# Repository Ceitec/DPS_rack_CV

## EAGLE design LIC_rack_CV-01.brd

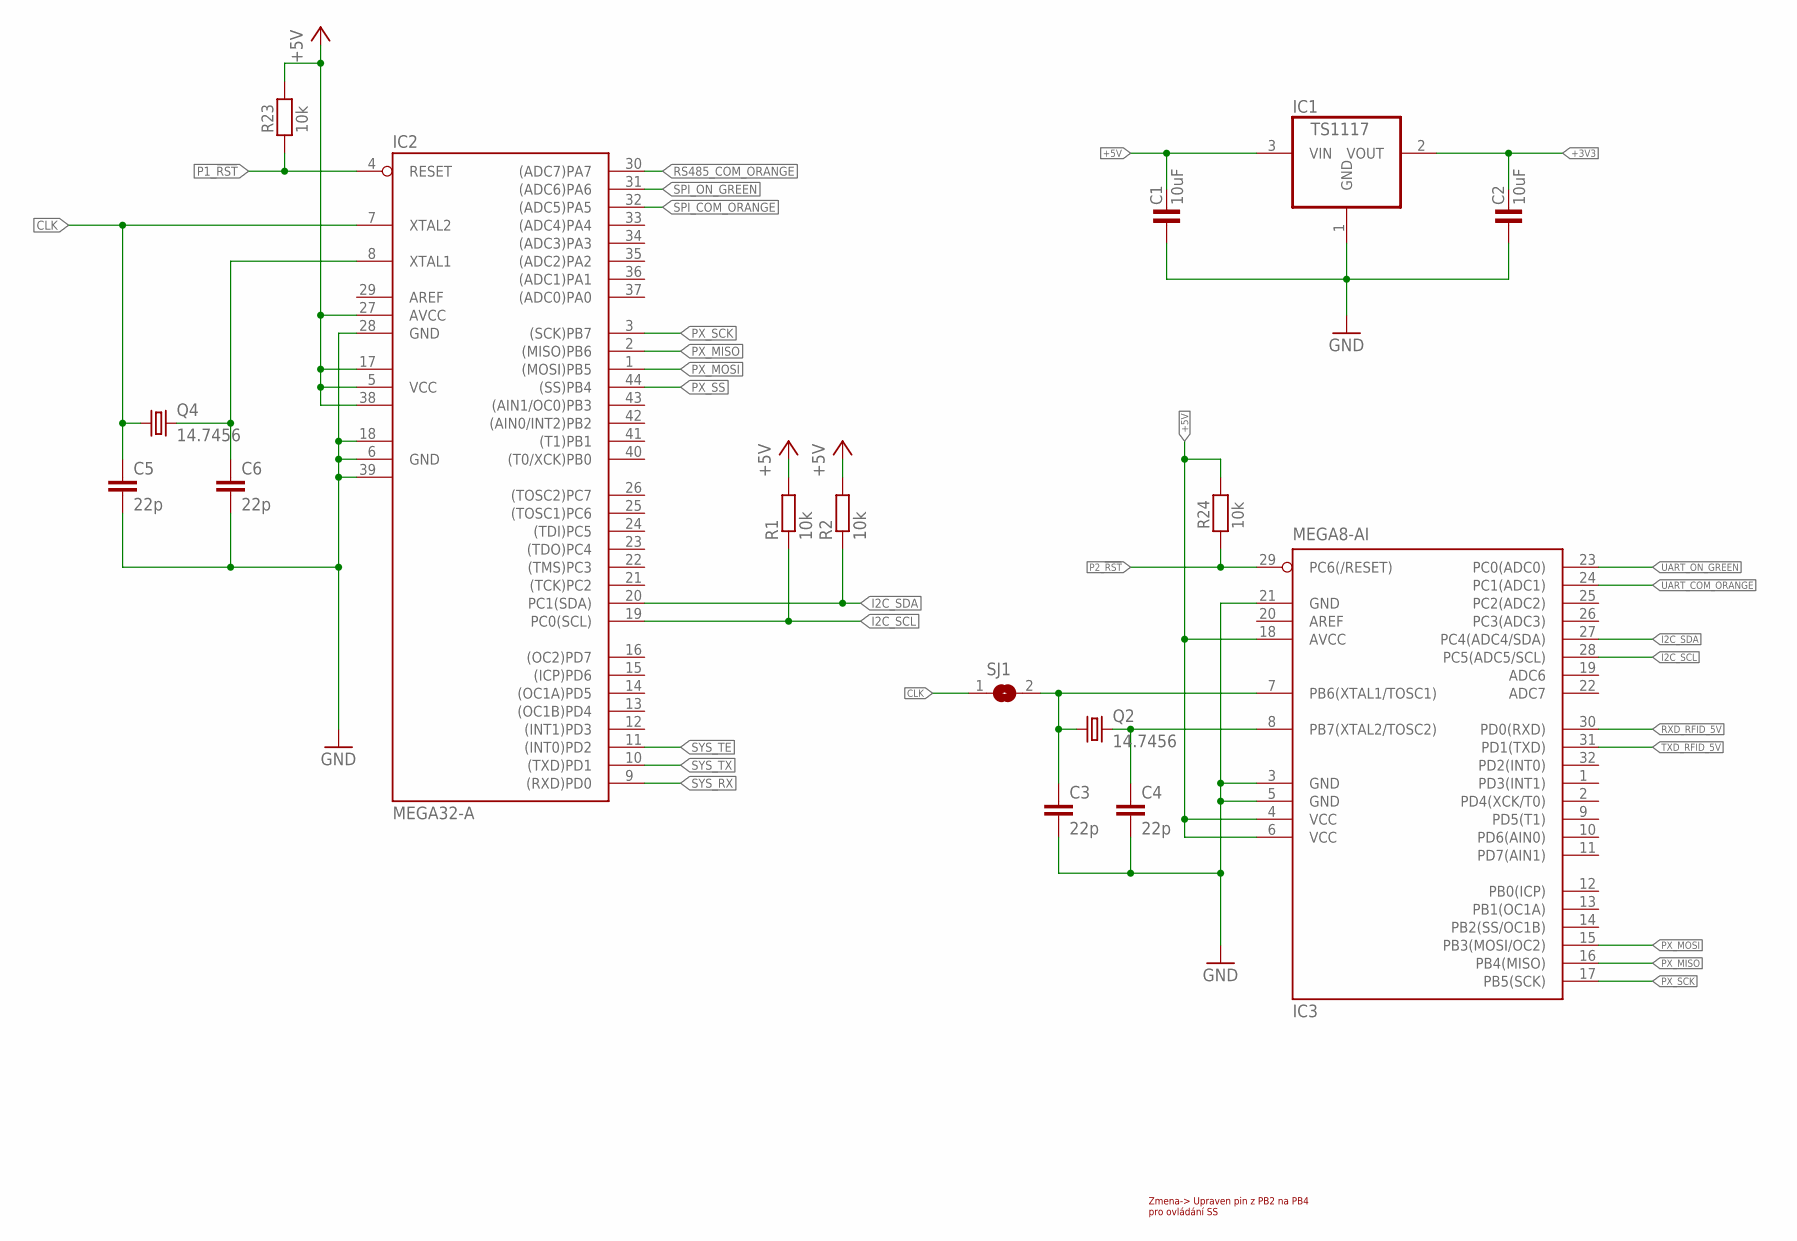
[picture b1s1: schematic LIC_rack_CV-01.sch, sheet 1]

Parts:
C1, C2: 10uF; 1206
C3, C4, C5, C6: 22p; C0805
IC1: TS1117; SOT223
IC2: MEGA32-A; TQFP44
IC3: MEGA8-AI; TQFP32-08
Q2, Q4: 14.7456; HC49U70
R1, R2: 10k; R1206
R23, R24: 10k; 1206
SJ1: SJ

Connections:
+3V3: C2.2, IC1.2 (VOUT); also elsewhere on the board
+5V: C1.2, IC1.3 (VIN), IC2.5 (VCC), IC2.17 (VCC1), IC2.27 (AVCC), IC2.38 (VCC2), IC3.4 (VCC), IC3.6 (VCC), IC3.18 (AVCC), R1.2, R2.2, R23.2, R24.2; also elsewhere on the board
CLK: C5.1, IC2.7 (XTAL2), Q4.1, SJ1.1
CLK1: C3.1, IC3.7 (PB6(XTAL1/TOSC1)), Q2.1, SJ1.2
GND: C1.1, C2.1, C3.2, C4.2, C5.2, C6.2, IC1.1 (GND), IC2.6 (GND), IC2.18 (GND1), IC2.28 (GND), IC2.39 (GND2), IC3.3 (GND), IC3.5 (GND), IC3.21 (GND); also elsewhere on the board
I2C_SCL: IC2.19 (PC0(SCL)), IC3.28 (PC5(ADC5/SCL)), R1.1
I2C_SDA: IC2.20 (PC1(SDA)), IC3.27 (PC4(ADC4/SDA)), R2.1
unnamed: C4.1, IC3.8 (PB7(XTAL2/TOSC2)), Q2.2
unnamed: C6.1, IC2.8 (XTAL1), Q4.2
P1_!RST: IC2.4 (RESET), R23.1; also elsewhere on the board
P2_!RST: IC3.29 (PC6(/RESET)), R24.1; also elsewhere on the board
PX_MISO: IC2.2 ((MISO)PB6), IC3.16 (PB4(MISO)); also elsewhere on the board
PX_MOSI: IC2.1 ((MOSI)PB5), IC3.15 (PB3(MOSI/OC2)); also elsewhere on the board
PX_SCK: IC2.3 ((SCK)PB7), IC3.17 (PB5(SCK)); also elsewhere on the board
PX_SS: IC2.44 ((SS)PB4); also elsewhere on the board
RS485_COM_ORANGE: IC2.30 ((ADC7)PA7); also elsewhere on the board
RXD_RFID_5V: IC3.30 (PD0(RXD)); also elsewhere on the board
SPI_COM_ORANGE: IC2.32 ((ADC5)PA5); also elsewhere on the board
SPI_ON_GREEN: IC2.31 ((ADC6)PA6); also elsewhere on the board
SYS_RX: IC2.9 ((RXD)PD0); also elsewhere on the board
SYS_TE: IC2.11 ((INT0)PD2); also elsewhere on the board
SYS_TX: IC2.10 ((TXD)PD1); also elsewhere on the board
TXD_RFID_5V: IC3.31 (PD1(TXD)); also elsewhere on the board
UART_COM_ORANGE: IC3.24 (PC1(ADC1)); also elsewhere on the board
UART_ON_GREEN: IC3.23 (PC0(ADC0)); also elsewhere on the board

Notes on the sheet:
Zmena-> Upraven pin z PB2 na PB4 pro ovládání SS

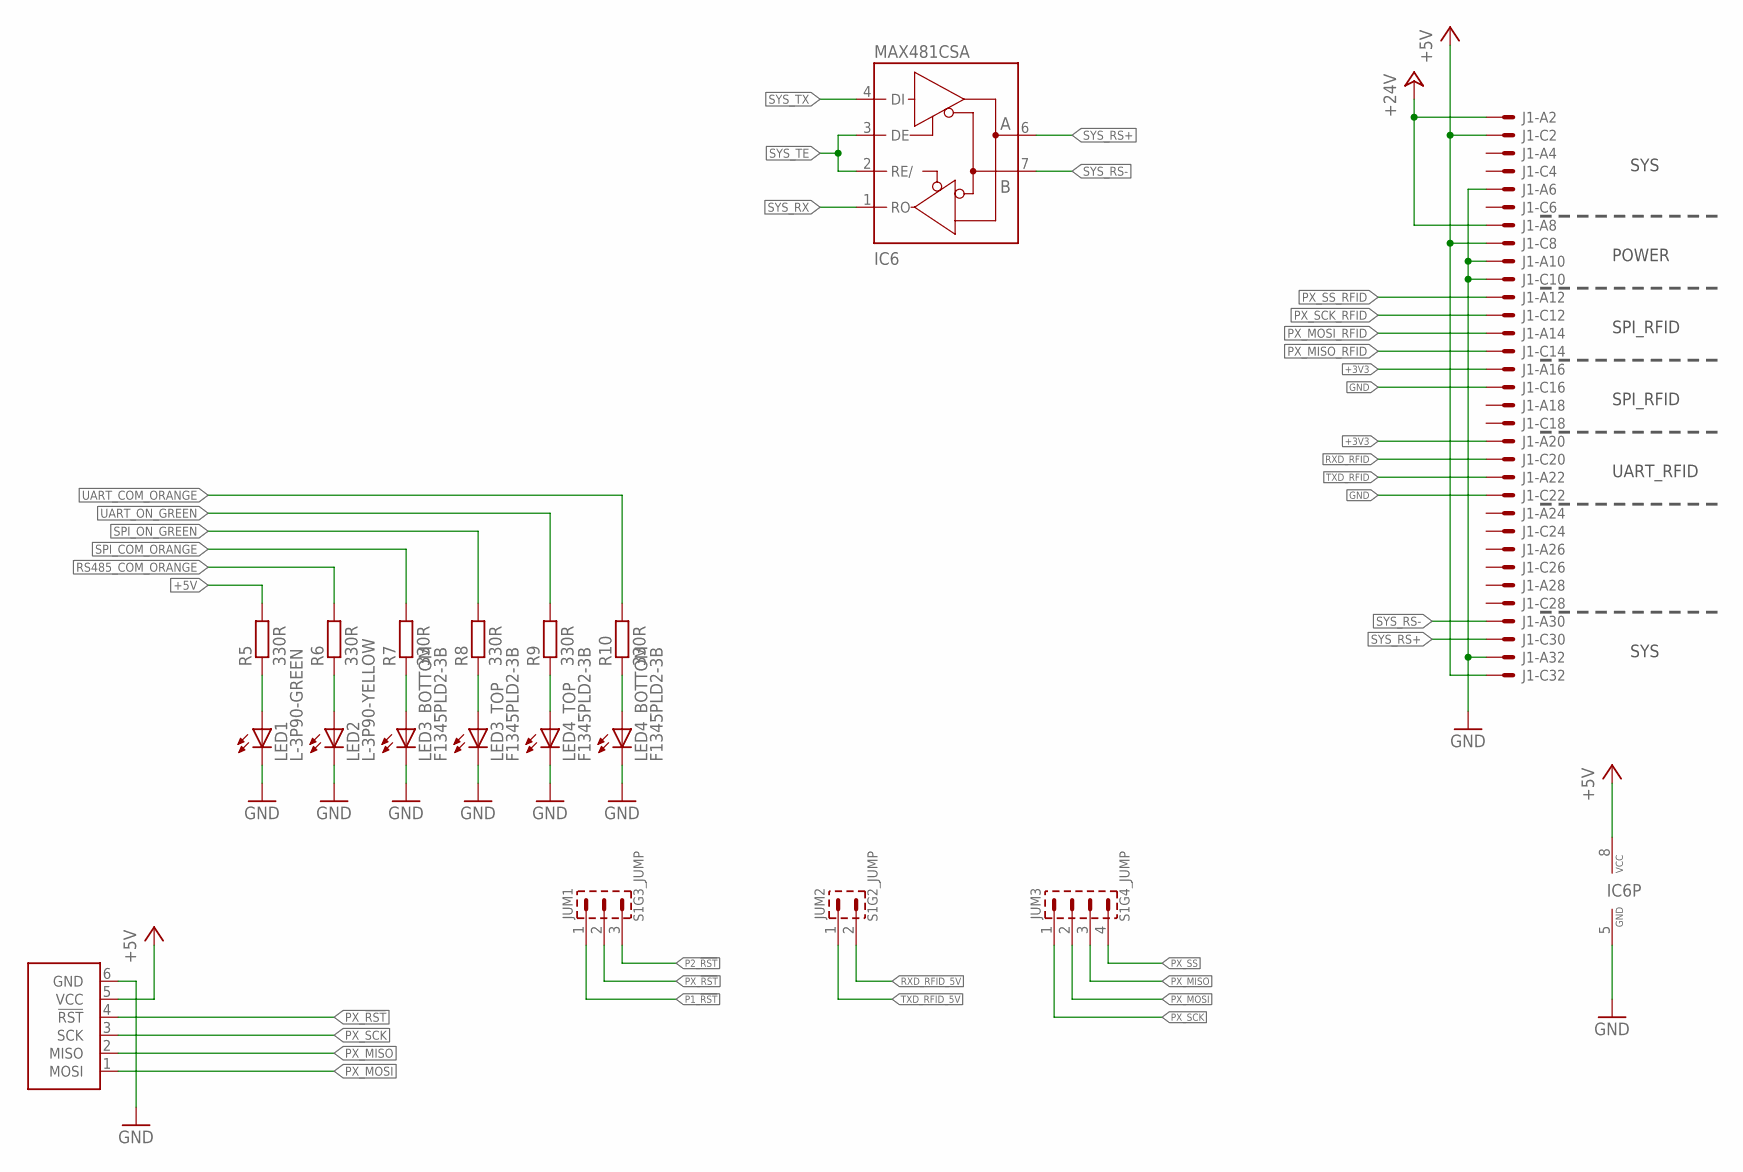
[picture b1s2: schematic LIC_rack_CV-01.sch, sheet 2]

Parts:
IC6: MAX481CSA; SO08
J1: VG32SP; VG32P
JUM1: S1G3_JUMP; S1G3_JUM
JUM2: S1G2_JUMP; S1G2_JUM
JUM3: S1G4_JUMP; S1G4_JUM
LED1: L-3P90-GREEN; L-3P90
LED2: L-3P90-YELLOW; L-3P90
LED3, LED4: F1345PLD2-3B
R5, R6, R7, R8, R9, R10: 330R; R1206
U1: ATPROG-V; 6410-06

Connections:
+3V3: J1.A16 (MS), J1.A20 (MS); also elsewhere on the board
+5V: IC6.8 (VCC), J1.C2 (MS), J1.C8 (MS), J1.C32 (MSV), R5.2, U1.5 (VCC); also elsewhere on the board
+24V: J1.A2 (MS), J1.A8 (MS)
GND: IC6.5 (GND), J1.A6 (MS), J1.A10 (MS), J1.A32 (MS), J1.C10 (MS), J1.C16 (MS), J1.C22 (MS), LED1.K (C), LED2.K (C), LED3.1K (C), LED3.2K (C), LED4.1K (C), LED4.2K (C), U1.6 (GND); also elsewhere on the board
unnamed: LED2.A, R6.1
unnamed: LED1.A, R5.1
unnamed: LED4.1A (A), R10.1
unnamed: LED4.2A (A), R9.1
unnamed: LED3.2A (A), R8.1
unnamed: LED3.1A (A), R7.1
P1_!RST: JUM1.1; also elsewhere on the board
P2_!RST: JUM1.3; also elsewhere on the board
PX_!RST: JUM1.2, U1.4 (!RST)
PX_MISO: JUM3.3, U1.2 (MISO); also elsewhere on the board
PX_MISO_RFID: J1.C14 (MS); also elsewhere on the board
PX_MOSI: JUM3.2, U1.1 (MOSI); also elsewhere on the board
PX_MOSI_RFID: J1.A14 (MS); also elsewhere on the board
PX_SCK: JUM3.1, U1.3 (SCK); also elsewhere on the board
PX_SCK_RFID: J1.C12 (MS); also elsewhere on the board
PX_SS: JUM3.4; also elsewhere on the board
PX_SS_RFID: J1.A12 (MS); also elsewhere on the board
RS485_COM_ORANGE: R6.2; also elsewhere on the board
RXD_RFID: J1.C20 (MS); also elsewhere on the board
RXD_RFID_5V: JUM2.2; also elsewhere on the board
SPI_COM_ORANGE: R7.2; also elsewhere on the board
SPI_ON_GREEN: R8.2; also elsewhere on the board
SYS_RS+: IC6.6 (A), J1.C30 (MS)
SYS_RS-: IC6.7 (B), J1.A30 (MS)
SYS_RX: IC6.1 (RO); also elsewhere on the board
SYS_TE: IC6.2 (RE/), IC6.3 (DE); also elsewhere on the board
SYS_TX: IC6.4 (DI); also elsewhere on the board
TXD_RFID: J1.A22 (MS); also elsewhere on the board
TXD_RFID_5V: JUM2.1; also elsewhere on the board
UART_COM_ORANGE: R10.2; also elsewhere on the board
UART_ON_GREEN: R9.2; also elsewhere on the board

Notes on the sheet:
SYS
POWER
SPI_RFID
UART_RFID

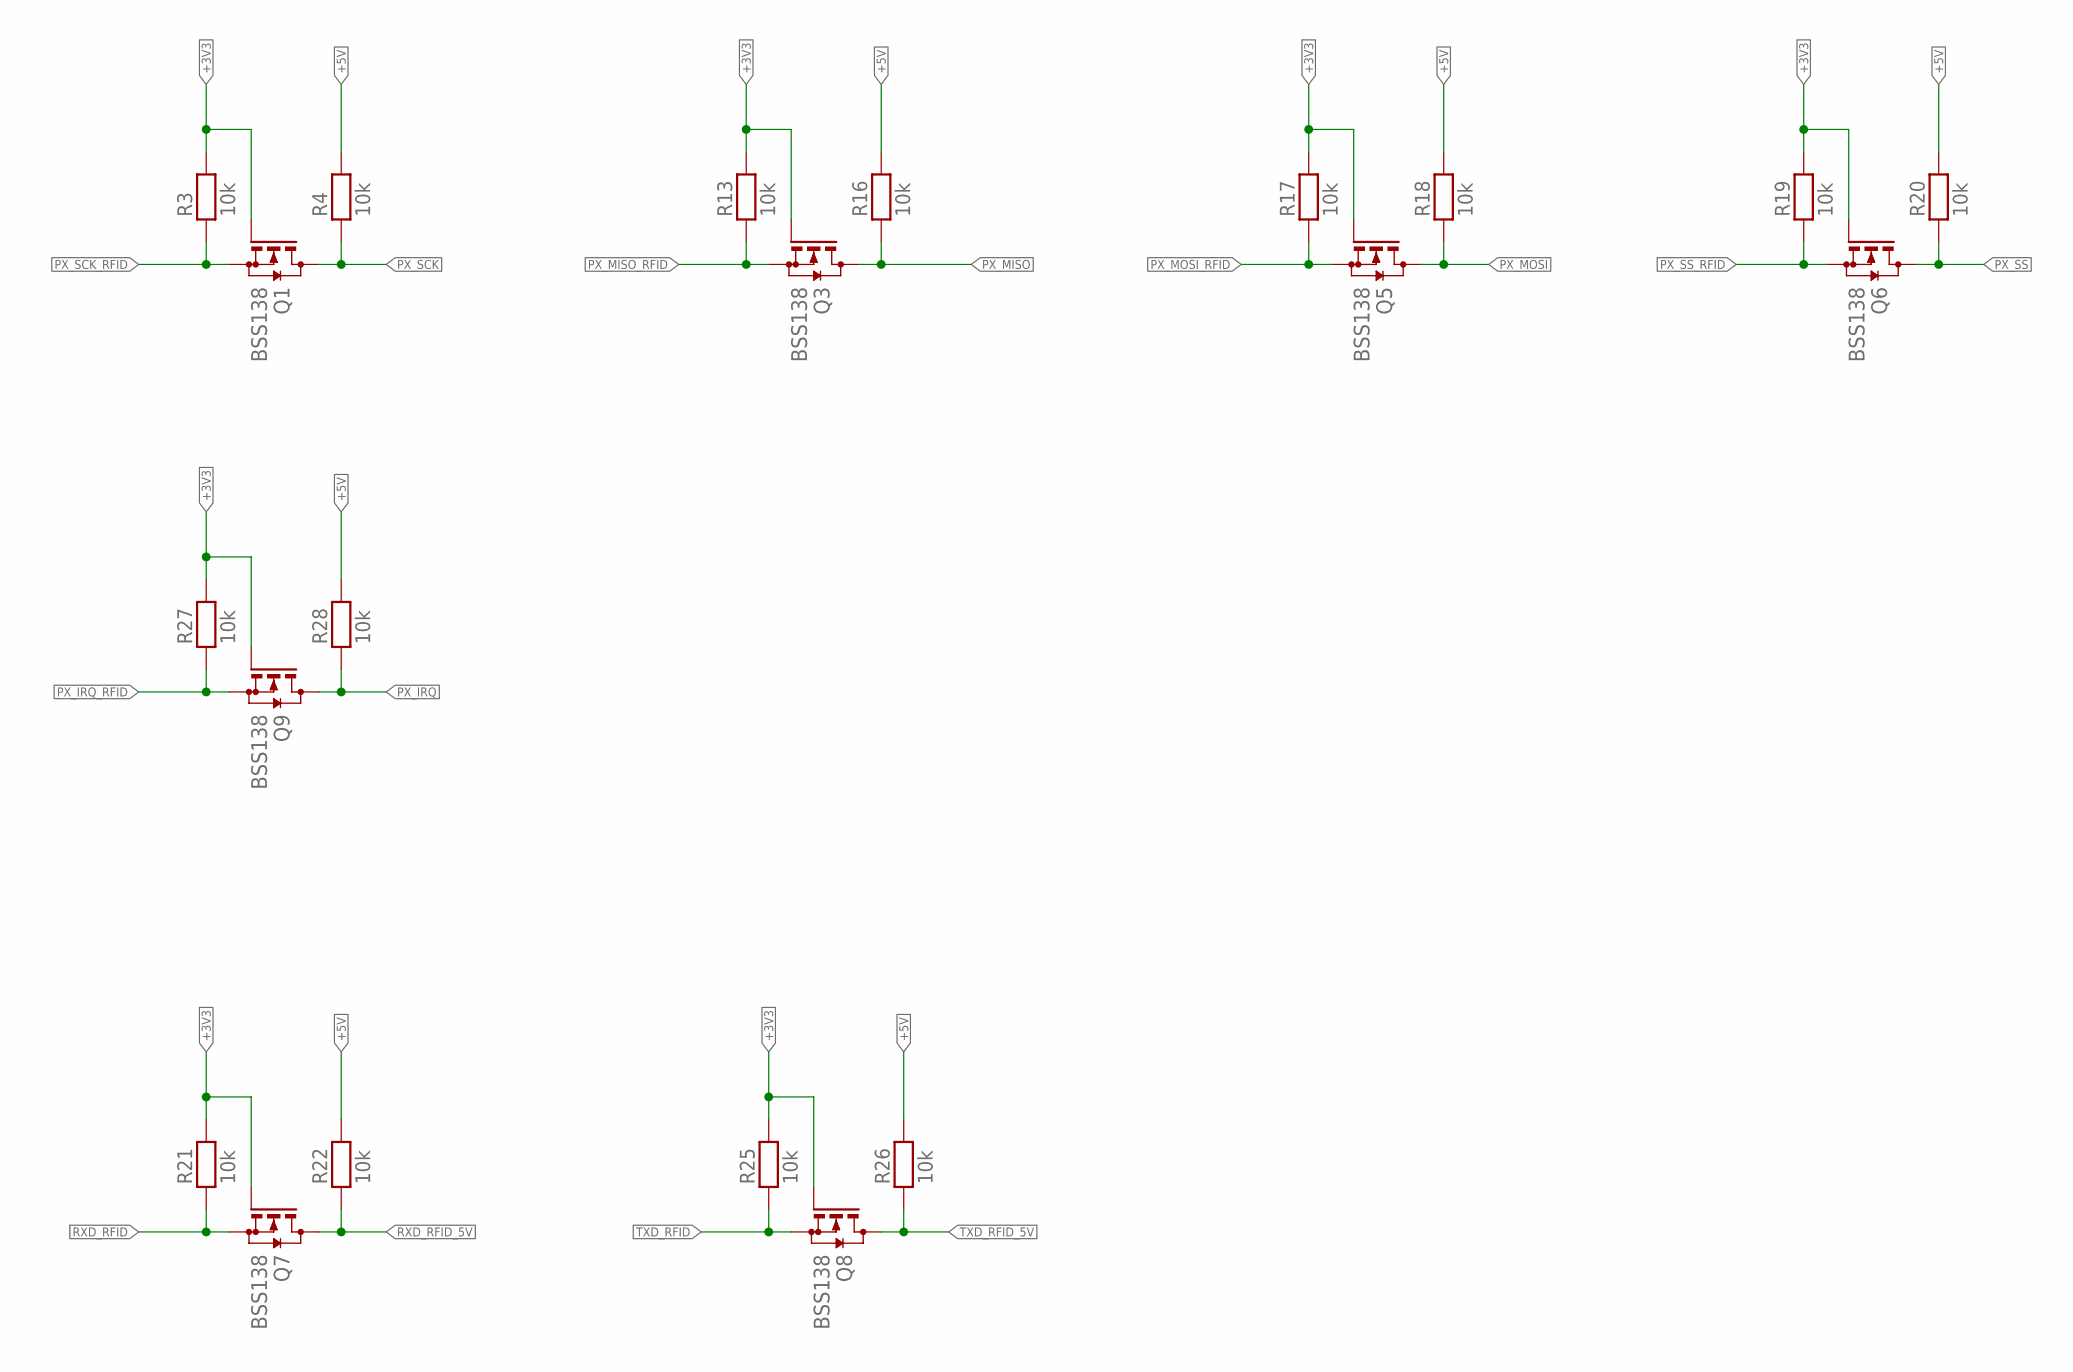
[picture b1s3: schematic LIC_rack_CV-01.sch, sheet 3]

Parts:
Q1, Q3, Q5, Q6, Q7, Q8, Q9: BSS138; SOT23
R3, R4, R13, R16, R17, R18, R19, R20, R21, R22, R25, R26, R27, R28: 10k; 1206

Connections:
+3V3: Q1.1 (G), Q3.1 (G), Q5.1 (G), Q6.1 (G), Q7.1 (G), Q8.1 (G), Q9.1 (G), R3.2, R13.2, R17.2, R19.2, R21.2, R25.2, R27.2; also elsewhere on the board
+5V: R4.2, R16.2, R18.2, R20.2, R22.2, R26.2, R28.2; also elsewhere on the board
PX_IRQ: Q9.3 (D), R28.1
PX_IRQ_RFID: Q9.2 (S), R27.1
PX_MISO: Q3.3 (D), R16.1; also elsewhere on the board
PX_MISO_RFID: Q3.2 (S), R13.1; also elsewhere on the board
PX_MOSI: Q5.3 (D), R18.1; also elsewhere on the board
PX_MOSI_RFID: Q5.2 (S), R17.1; also elsewhere on the board
PX_SCK: Q1.3 (D), R4.1; also elsewhere on the board
PX_SCK_RFID: Q1.2 (S), R3.1; also elsewhere on the board
PX_SS: Q6.3 (D), R20.1; also elsewhere on the board
PX_SS_RFID: Q6.2 (S), R19.1; also elsewhere on the board
RXD_RFID: Q7.2 (S), R21.1; also elsewhere on the board
RXD_RFID_5V: Q7.3 (D), R22.1; also elsewhere on the board
TXD_RFID: Q8.2 (S), R25.1; also elsewhere on the board
TXD_RFID_5V: Q8.3 (D), R26.1; also elsewhere on the board

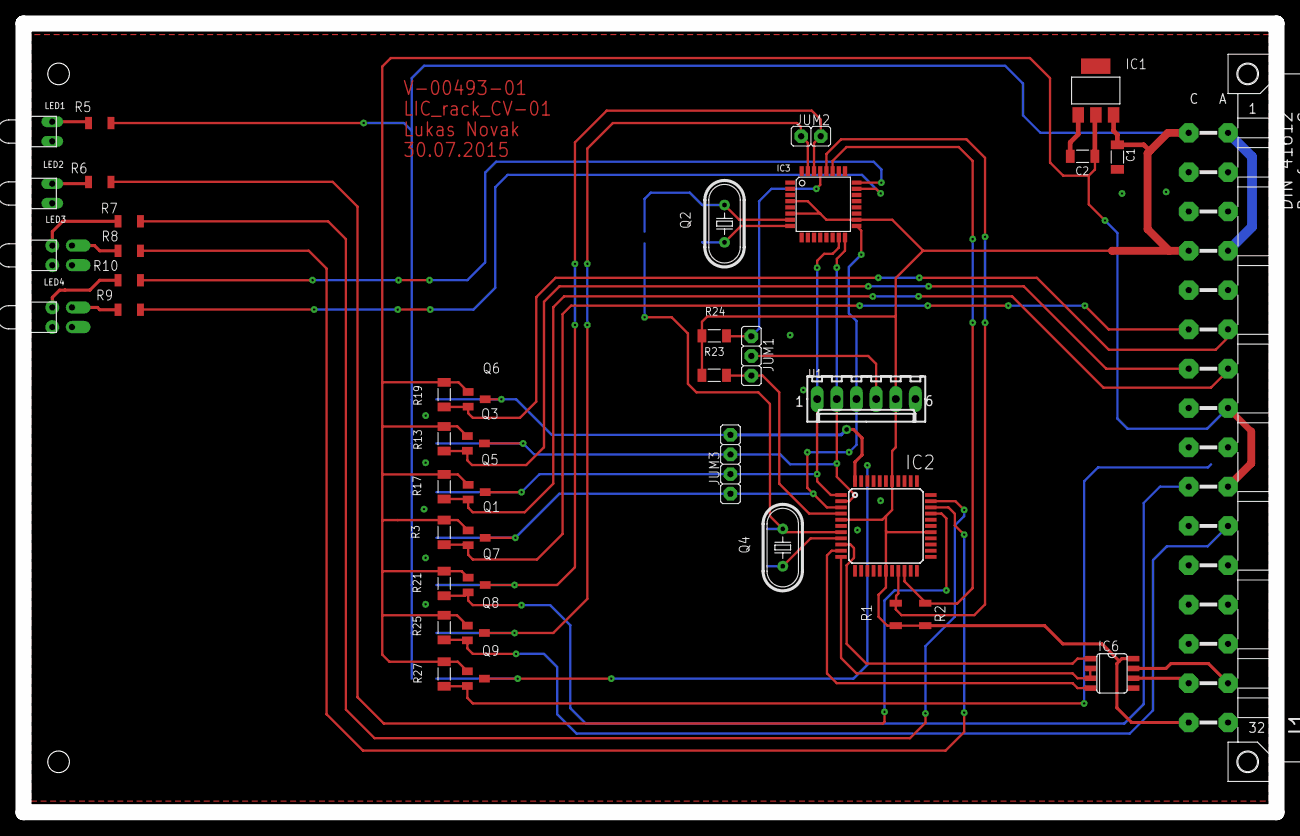
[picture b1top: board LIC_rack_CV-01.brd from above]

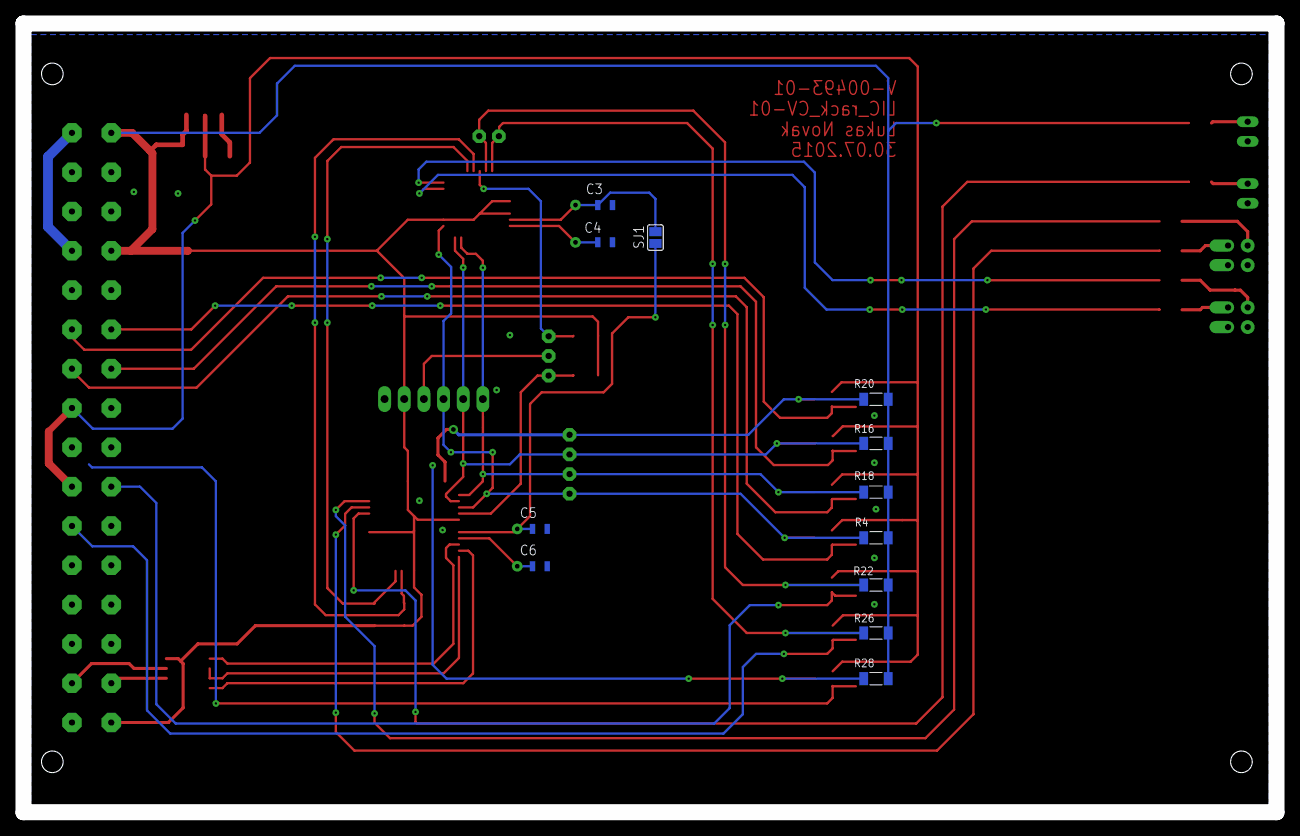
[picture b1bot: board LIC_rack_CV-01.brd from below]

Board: 2 copper layers, 162.0 x 102.0 mm, 53 parts (12 on the bottom side), 43 nets.

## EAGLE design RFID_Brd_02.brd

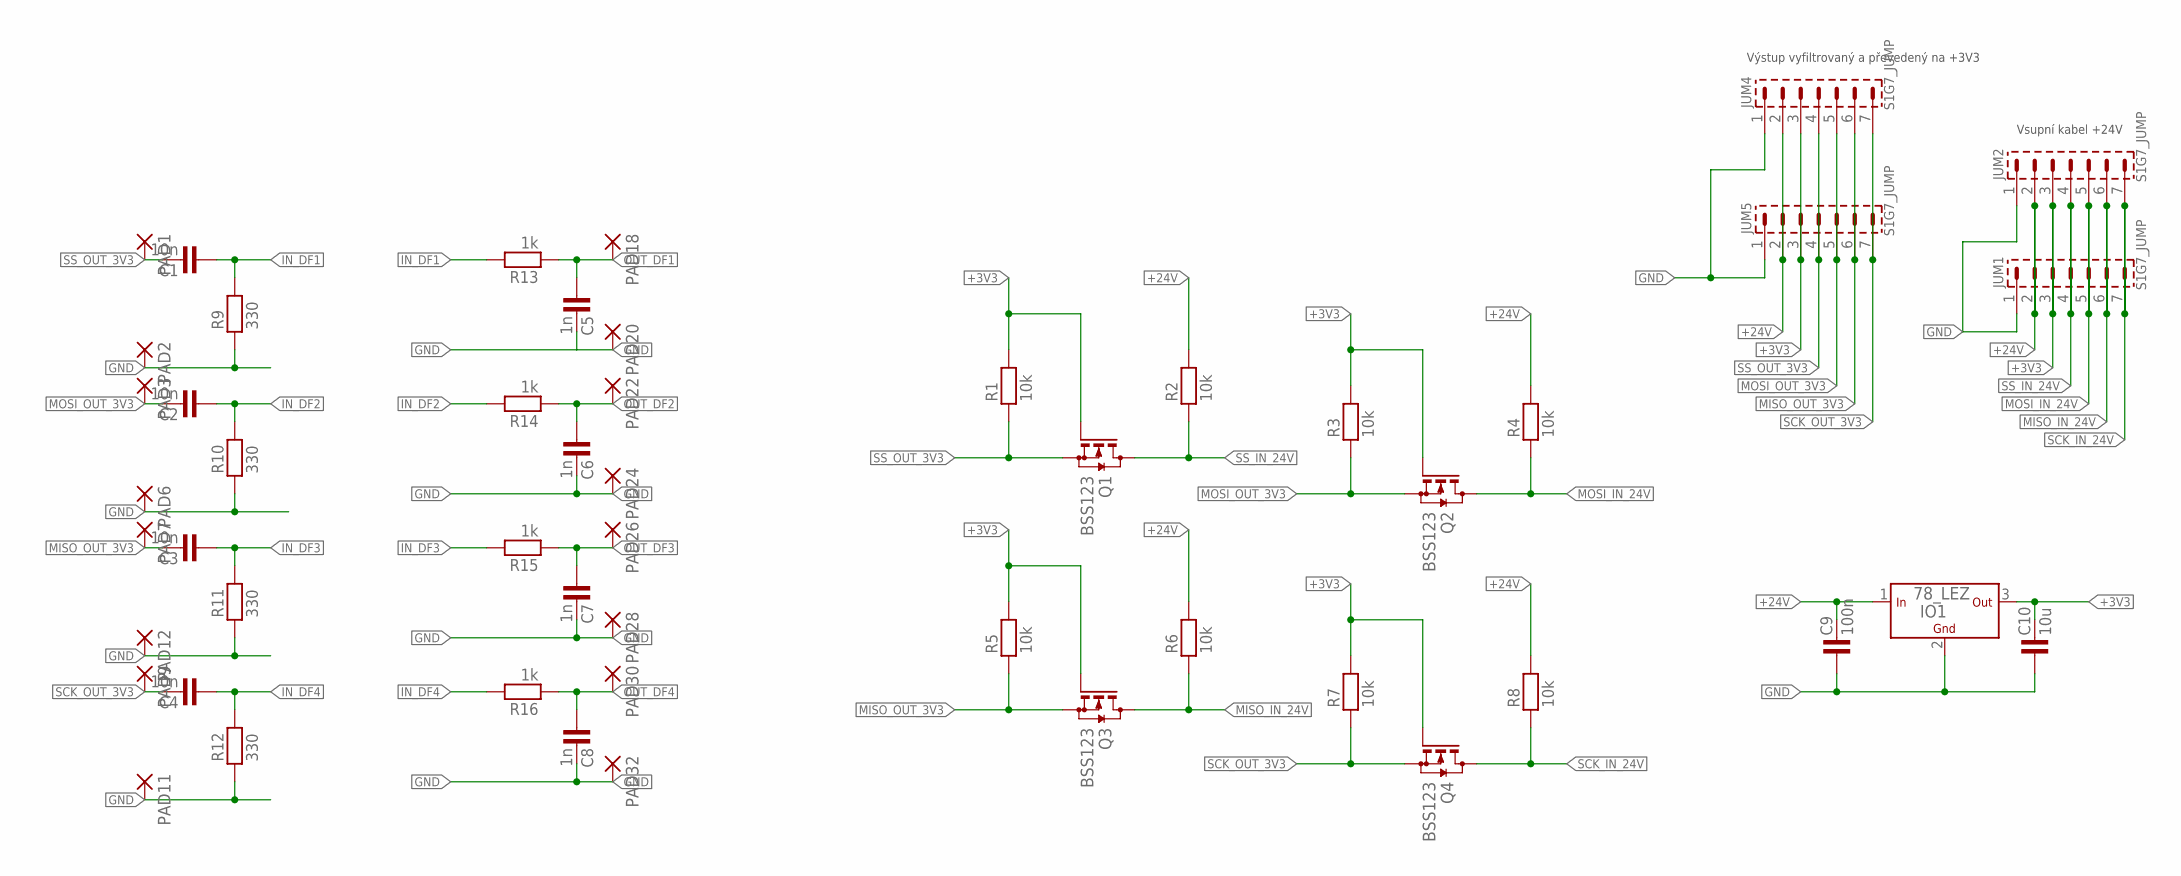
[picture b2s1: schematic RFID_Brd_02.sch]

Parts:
C1, C2, C3, C4: 10n; 1206
C5, C6, C7, C8: 1n; 1206
C9: 100n; 1206
C10: 10u; 1206
IO1: 78_LEZ; TO-220
JUM1, JUM2, JUM4, JUM5: S1G7_JUMP; S1G7_JUM
PAD1, PAD2, PAD3, PAD6, PAD7, PAD9, PAD11, PAD12, PAD18, PAD20, PAD22, PAD24, PAD26, PAD28, PAD30, PAD32: SMD2; SMD1,27-2,54
Q1, Q2, Q3, Q4: BSS123; SOT23
R1, R2, R3, R4, R5, R6, R7, R8: 10k; 1206
R9, R10, R11, R12: 330; 1206
R13, R14, R15, R16: 1k; 1206

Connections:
+3V3: C10.2, IO1.3 (OUT), JUM1.3, JUM2.3, JUM4.3, JUM5.3, Q1.1 (G), Q2.1 (G), Q3.1 (G), Q4.1 (G), R1.2, R3.2, R5.2, R7.2
+24V: C9.2, IO1.1 (IN), JUM1.2, JUM2.2, JUM4.2, JUM5.2, R2.2, R4.2, R6.2, R8.2
GND: C5.2, C6.2, C7.2, C8.2, C9.1, C10.1, IO1.2 (GND), JUM1.1, JUM2.1, JUM4.1, JUM5.1, PAD2.1, PAD6.1, PAD11.1, PAD12.1, PAD20.1, PAD24.1, PAD28.1, PAD32.1, R9.1, R10.1, R11.1, R12.1
IN_DF1: C1.1, R9.2, R13.2
IN_DF2: C2.1, R10.2, R14.2
IN_DF3: C3.1, R11.2, R15.2
IN_DF4: C4.1, R12.2, R16.2
MISO_IN_24V: JUM1.6, JUM2.6, Q3.3 (D), R6.1
MISO_OUT_3V3: C3.2, JUM4.6, JUM5.6, PAD7.1, Q3.2 (S), R5.1
MOSI_IN_24V: JUM1.5, JUM2.5, Q2.3 (D), R4.1
MOSI_OUT_3V3: C2.2, JUM4.5, JUM5.5, PAD3.1, Q2.2 (S), R3.1
OUT_DF1: C5.1, PAD18.1, R13.1
OUT_DF2: C6.1, PAD22.1, R14.1
OUT_DF3: C7.1, PAD26.1, R15.1
OUT_DF4: C8.1, PAD30.1, R16.1
SCK_IN_24V: JUM1.7, JUM2.7, Q4.3 (D), R8.1
SCK_OUT_3V3: C4.2, JUM4.7, JUM5.7, PAD9.1, Q4.2 (S), R7.1
SS_IN_24V: JUM1.4, JUM2.4, Q1.3 (D), R2.1
SS_OUT_3V3: C1.2, JUM4.4, JUM5.4, PAD1.1, Q1.2 (S), R1.1

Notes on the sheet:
Vsupní kabel +24V
Výstup vyfiltrovaný a převedený na +3V3

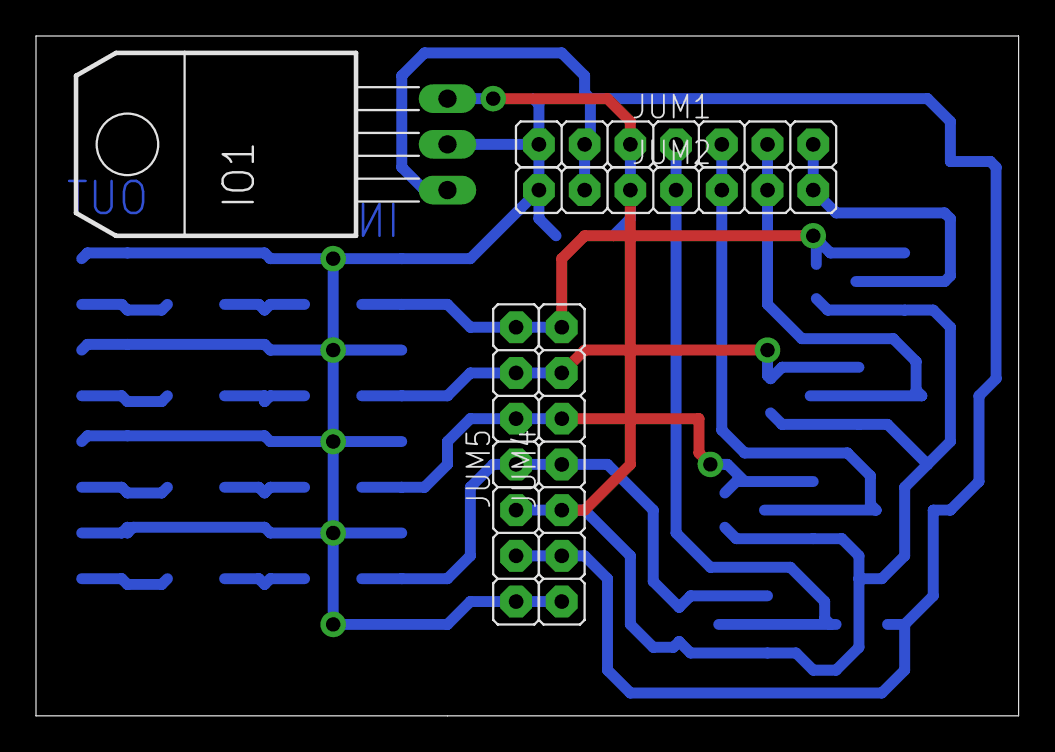
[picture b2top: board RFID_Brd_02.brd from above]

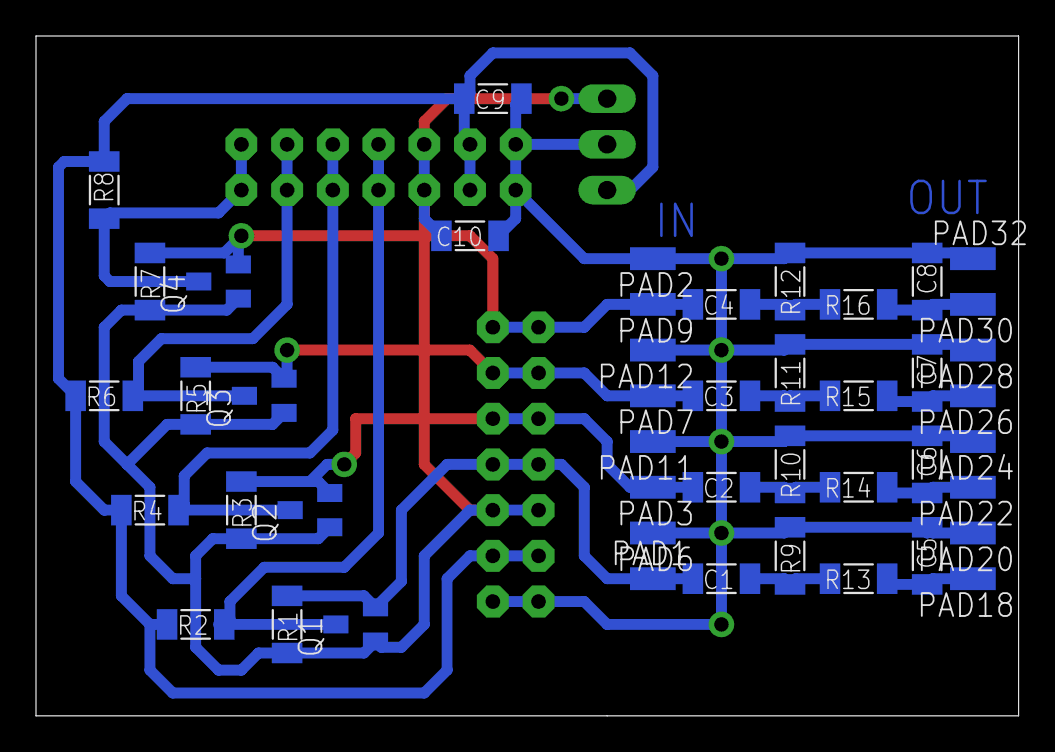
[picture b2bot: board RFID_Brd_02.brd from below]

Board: 2 copper layers, 54.6 x 37.8 mm, 51 parts (46 on the bottom side), 19 nets.

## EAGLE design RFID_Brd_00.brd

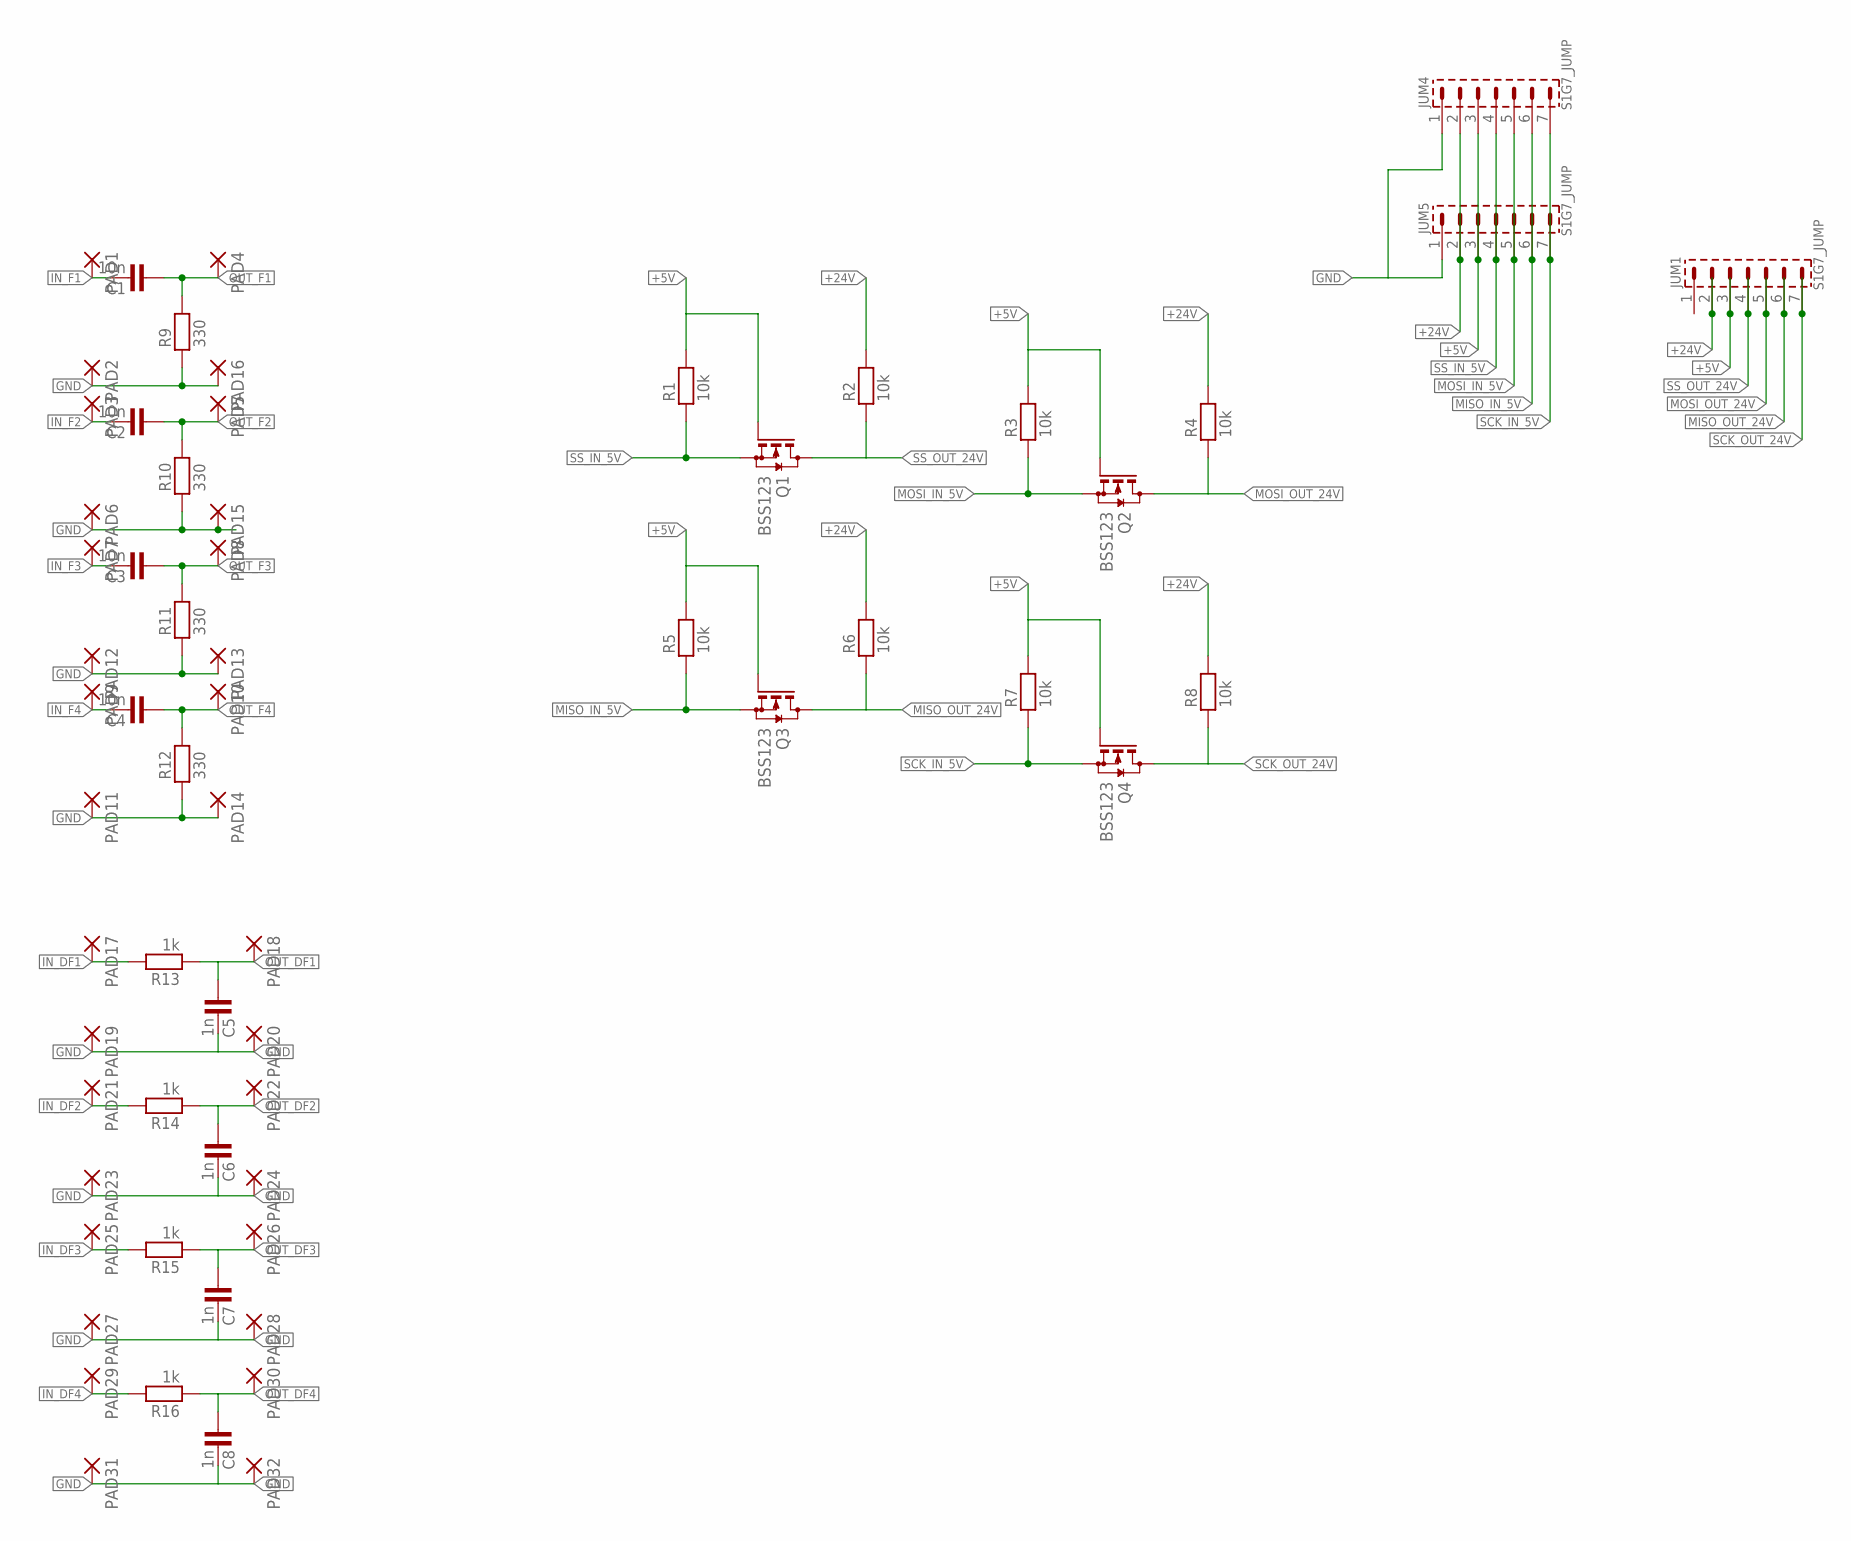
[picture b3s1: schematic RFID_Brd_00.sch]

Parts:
C1, C2, C3, C4: 10n; 1206
C5, C6, C7, C8: 1n; 1206
JUM1, JUM4, JUM5: S1G7_JUMP; S1G7_JUM
PAD1, PAD2, PAD3, PAD4, PAD5, PAD6, PAD7, PAD8, PAD9, PAD10, PAD11, PAD12, PAD13, PAD14, PAD15, PAD16, PAD17, PAD18, PAD19, PAD20, PAD21, PAD22, PAD23, PAD24, PAD25, PAD26, PAD27, PAD28, PAD29, PAD30, PAD31, PAD32: SMD2; SMD1,27-2,54
Q1, Q2, Q3, Q4: BSS123; SOT23
R1, R2, R3, R4, R5, R6, R7, R8: 10k; 1206
R9, R10, R11, R12: 330; 1206
R13, R14, R15, R16: 1k; 1206

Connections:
+5V: JUM1.3, JUM4.3, JUM5.3, Q1.1 (G), Q2.1 (G), Q3.1 (G), Q4.1 (G), R1.2, R3.2, R5.2, R7.2
+24V: JUM1.2, JUM4.2, JUM5.2, R2.2, R4.2, R6.2, R8.2
GND: C5.2, C6.2, C7.2, C8.2, JUM4.1, JUM5.1, PAD2.1, PAD6.1, PAD11.1, PAD12.1, PAD13.1, PAD14.1, PAD15.1, PAD16.1, PAD19.1, PAD20.1, PAD23.1, PAD24.1, PAD27.1, PAD28.1, PAD31.1, PAD32.1, R9.1, R10.1, R11.1, R12.1
IN_DF1: PAD17.1, R13.2
IN_DF2: PAD21.1, R14.2
IN_DF3: PAD25.1, R15.2
IN_DF4: PAD29.1, R16.2
IN_F1: C1.2, PAD1.1
IN_F2: C2.2, PAD3.1
IN_F3: C3.2, PAD7.1
IN_F4: C4.2, PAD9.1
MISO_IN_5V: JUM4.6, JUM5.6, Q3.2 (S), R5.1
MISO_OUT_24V: JUM1.6, Q3.3 (D), R6.1
MOSI_IN_5V: JUM4.5, JUM5.5, Q2.2 (S), R3.1
MOSI_OUT_24V: JUM1.5, Q2.3 (D), R4.1
OUT_DF1: C5.1, PAD18.1, R13.1
OUT_DF2: C6.1, PAD22.1, R14.1
OUT_DF3: C7.1, PAD26.1, R15.1
OUT_DF4: C8.1, PAD30.1, R16.1
OUT_F1: C1.1, PAD4.1, R9.2
OUT_F2: C2.1, PAD5.1, R10.2
OUT_F3: C3.1, PAD8.1, R11.2
OUT_F4: C4.1, PAD10.1, R12.2
SCK_IN_5V: JUM4.7, JUM5.7, Q4.2 (S), R7.1
SCK_OUT_24V: JUM1.7, Q4.3 (D), R8.1
SS_IN_5V: JUM4.4, JUM5.4, Q1.2 (S), R1.1
SS_OUT_24V: JUM1.4, Q1.3 (D), R2.1

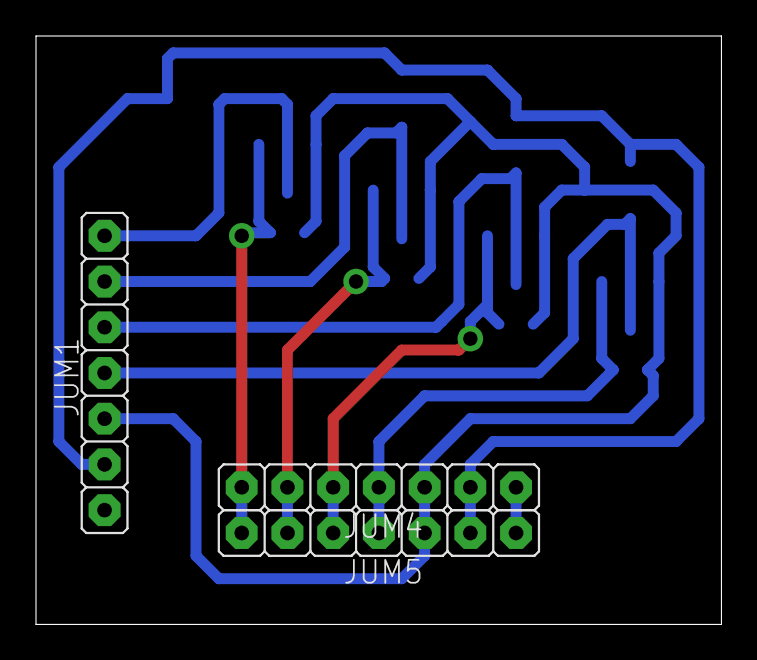
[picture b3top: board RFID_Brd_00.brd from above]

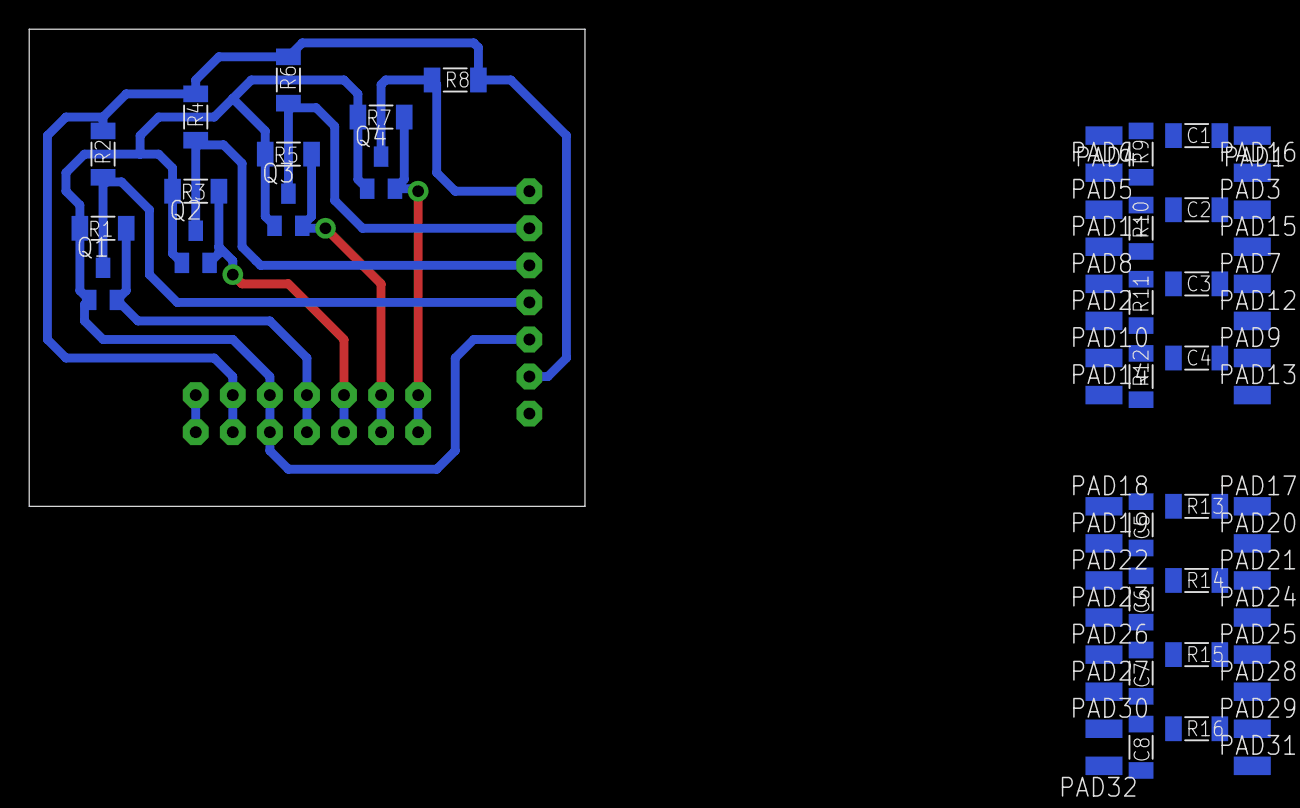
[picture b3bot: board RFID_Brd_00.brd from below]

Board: 2 copper layers, 38.1 x 32.7 mm, 63 parts (60 on the bottom side), 27 nets.

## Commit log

2015-08-11 :circus_tent: Added .gitattributes & .gitignore files
2015-08-11 Čtení vzorků
2015-08-18 Dalsi verze
    Upravena deska skrz SS pin
2015-09-16 Dalsi upravy
2015-09-25 A
    A
2015-11-22 Knihovna LED pridana sem
2015-11-22 Uprava knihoven

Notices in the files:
parts and their libraries:
Copyright (C) PaJa 2001-2014
Copyright (C) PaJa 2011-2014
